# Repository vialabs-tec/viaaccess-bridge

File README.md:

# ViaAccess Bridge

Sidecar que conecta **Frigate** ao [ViaAccess](https://viaaccess.dev) via [VADP](https://viaaccess.dev/docs/detection-providers/vadp).

```
Câmeras → Frigate → MQTT → viaaccess-bridge → POST /api/v1/detections → ViaAccess
```

O bridge **não** faz reconhecimento facial nem cadastro de usuários. Ele traduz eventos de zona do Frigate em detecções de passagem (`passage_detected`) para auditoria no ViaAccess.

## Instalação

Pacote pronto com Frigate + MQTT + bridge: **[install/frigate/](install/frigate/README.md)**.

Leitor de QR na catraca + QR dinâmico Identity (Phase 1b): appliance
**[install/qr-reader-firmware/](install/qr-reader-firmware/README.md)** (ESP32-S3, ESP-IDF).
Contrato HTTP na porta 3710 e endpoints `/api/bridge/*` do Identity.

O agent Go em [install/qr-reader-agent/](install/qr-reader-agent/README.md) (Raspberry Pi)
é **legado**: código permanece no repo, CI desligado, sem novas instalações nem OTA de frota.

| | ESP32-S3 (suportado) |
|---|---|
| Leitor de QR | UART TTL 9600 (ex. EP8280L) ou `POST /scan` |
| Rede na primeira vez | SoftAP `viaaccess-setup` → `/wifi` |
| Mapa de GPIO | relé 10, porta 11, REX 12, LED 4/5/6 |
| Relógio | SNTP; DS3231 opcional para hora confiável sem rede |
| Contingência offline | Implementada (inclui `after_hours`) |
| OTA de frota | App image via comando `UPDATE` (`BRIDGE_OTA_*`) |

Provisionamento: cole a URL de claim (`clm_…`) do admin do Identity em
`http://viaaccess.local:3710/setup`.

Imagem Docker:

```text
ghcr.io/vialabs-tec/viaaccess-bridge:latest
```

```bash
cd install/frigate
cp .env.example .env   # API key + mapping
docker compose pull
docker compose up -d
```

Crie o tenant, o ponto de acesso (slug) e a API key no painel ViaAccess antes de subir o compose. Documentação completa: [viaaccess.dev/docs](https://viaaccess.dev/docs).

## Variáveis

| Variável | Descrição |
|----------|-----------|
| `VIAACCESS_API_URL` | URL da API ViaAccess |
| `VIAACCESS_API_KEY` | API key do tenant (`vac_…`) |
| `FRIGATE_MQTT_URL` | Broker MQTT (no compose: `mqtt://mqtt:1883`) |
| `FRIGATE_BASE_URL` | API HTTP do Frigate (snapshots) |
| `FRIGATE_ACCESS_POINT_MAP` | JSON: câmera + zona → slug do access point |
| `presenceSessionGapSeconds` | (por mapping) debounce de movimento contínuo no interior — ver README |
| `OUTBOX_PATH` | Fila de retry quando a API está offline |
| `BRIDGE_STATUS_PATH` | Arquivo JSON de status (opcional) |

## Desenvolvimento

```bash
npm install
cp .env.example .env
npm run dev
npm test
```

Build local da imagem: `npm run docker:build`

## Licença

Software proprietário © Via Labs. Uso sujeito aos termos do serviço ViaAccess.

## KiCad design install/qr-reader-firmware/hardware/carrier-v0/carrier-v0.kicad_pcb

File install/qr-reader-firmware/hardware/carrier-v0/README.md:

# Carrier v0 — KiCad project

Pilot interconnect PCB for the ESP32-S3 QR Reader appliance. Replaces Dupont
spaghetti: field screw terminals + module headers + 5 V star.

Spec: [`docs/carrier-v0.md`](../../docs/carrier-v0.md)

**Enclosure:** keep LOCK / DOOR / REX / READER screw terminals **inside** the
case. Field cables enter through **PG cable glands**; strain-relieve the jacket
(gland + cable tie) before the block. See *Case cable entry and strain relief*
in the spec — do not put live screw terminals on the outside of the case.
Mechanical project: [`../case-v0/`](../case-v0/) (FreeCAD workflow + OpenSCAD
skeleton).

| File | Role |
|---|---|
| `carrier-v0.kicad_pro` | KiCad 8+ project |
| `carrier-v0.kicad_pcb` | Board (footprints, routed nets, GND pour on `B.Cu`) |
| `carrier-v0.kicad_sch` | Net / connector index (minimal graphics) |
| `gen_pcb.py` | Regenerates the PCB (pad-accurate Manhattan routes) |
| `fab/` | JLCPCB Gerber/BOM/CPL notes |

Board size: **90 × 60 mm**, 2-layer, 1.6 mm.

Regenerate after layout edits in the script:

```bash
python3 gen_pcb.py
```

**Quit KiCad fully** (not only the PCB editor), then reopen `carrier-v0.kicad_pro`.
**Fill all zones**, then **DRC**.

### Routing status (v0)

Autorouted (corridor A\* on F/B + vias) with `B.Cu` GND pour. After regenerate:
quit KiCad fully → reopen → **Fill all zones** → **DRC**.
Pads-only fallback: `UNROUTED = True` in `gen_pcb.py`.

## Design choices

- **J1 DCIN** is a **XH 2P wafer** (pitch 2.5 mm, market “XH2.54”) for the
  female XH housing on the pigtail of a **panel-mount 5.5×2.1 mm** DC jack (P4).
  Pin 1 = `+5V`, pin 2 = `GND`. No field screw terminal for power.
- **J8A / J8B** are two **1×22** female headers (2.54 mm pitch) whose centers are
  **22.86 mm (0.9″)** apart — JLCPCB has no single dual-row 0.9″ part. Plug the
  DevKit **component-side up, USB to the left** (silk tick on J8A). Factory
  GPIOs/power on J8A (DevKit J1); J8B (DevKit J3) pads are NC keepouts.
  Pinout matches Espressif DevKitC-1 v1.1.
- **No BSS138 module.** Relay and buzzer use discrete **2N2222** open-collector
  drivers on the carrier (`Q2`/`R2`/`R3` and `Q1`/`R1`).
- **Relay (`J9`):** `IN` is pulled up to 5 V by `R3` (10k) and sunk by `Q2`
  when GPIO10 is high. In `/setup`, leave **relay active-high unchecked**
  (idle = GPIO high holds `IN` low / relay off; pulse drives GPIO low → `IN` high).
- **Buzzer (`J12`):** 2-wire active / SFM-20B. `+` → 5 V, `−` → `Q1` collector.
  In `/setup`, **buzzer active-high checked**.

### J8A / J8B DevKitC-1 nets (carrier)

USB end → far end. **J8A** = DevKit **J1**, **J8B** = DevKit **J3**.

| Socket | DevKit header | Pins netted on carrier |
|---|---|---|
| J8A | J1 | 3V3 (pin 1), GPIO 4–7, 17, 18, 8–12, 5V, GND |
| J8B | J3 | all NC on carrier (mechanical only) |

Reader UART on the carrier: GPIO17 = ESP RX, GPIO18 = ESP TX (factory map).

### NPN drivers (TO-92)

Pads left → right with flat face toward the silk “CBE” mark: **C – B – E**.

| Ref | C | B | E | Base resistor |
|---|---|---|---|---|
| Q2 (relay) | `RELAY_IN` | `Q2_BASE` | `GND` | R2 1k ← GPIO10 |
| Q1 (buzzer) | `BUZZ_SW` | `Q1_BASE` | `GND` | R1 1k ← GPIO7 |

Confirm against your transistor datasheet (2N2222 vs BC547 pinouts differ).

## Open in KiCad

1. Install [KiCad 8+](https://www.kicad.org/).
2. Open `carrier-v0.kicad_pro`.
3. Open the PCB: **Board Editor**.
4. Run **Fill all zones** (B.Cu GND pour) and **DRC**.
5. Tweak track positions if your module body keepouts need space.

The PCB was generated by script so expect to nudge silkscreen and re-pour GND
once before fab.

## Export Gerbers for JLCPCB

1. PCB Editor → **File → Fabrication Outputs → Gerbers** (`gerbers/`).
2. Enable layers: `F.Cu`, `B.Cu`, `F.SilkS`, `B.SilkS`, `F.Mask`, `B.Mask`, `Edge.Cuts`.
3. **Generate drill files** (Excellon).
4. Zip the `gerbers/` folder → upload to JLCPCB.
5. Options that usually work: 2 layers, 1.6 mm, HASL, 1 oz copper.

Suggested first order: **5 pcs**.

### PCBA (passives + sockets + connectors + NPNs)

BOM + centroid: [`fab/`](fab/) (`bom-jlcpcb.csv`, `cpl-jlcpcb.csv`, steps in `fab/README.md`).

- Enable **Standard** PCB Assembly (THT + SMT), top side.
- Assemble C1/C2, headers, screw terminals, DevKit socket, Q1/Q2, R1/R2/R3.
- **Do not** assemble DevKit / relay module / buzzer / LED / RTC — those plug in.

## Assembly notes

1. If bare PCB: solder SMDs (C2, R3), then THT (C1, transistors, headers, terminals).
   If PCBA, skip to continuity / module plug-in.
2. Continuity: `P5V` not shorted to `GND`.
3. Power via panel DC jack → J1 DCIN only: ~5 V on star, ~3.3 V on J8A pin 1.
4. `/setup`: relay **active-high off**; buzzer **active-high on**.
5. See checklist in `docs/carrier-v0.md`.

## BOM (carrier PCB)

| Ref | Part | Notes |
|---|---|---|
| J1 | XH 2P wafer (2.5 mm) | DCIN — mates jack pigtail XH female |
| J2 | Screw terminal 3P 5.08 | LOCK |
| J3, J4 | Screw terminal 2P 5.08 | DOOR, REX |
| J5 | Screw terminal 4P 5.08 | READER |
| J8A, J8B | Female header 1×22 ×2 | ESP32-S3-DevKitC-1 socket (0.9″ spacing) |
| J9, J10 | Pin header 1×3 | Relay control + dry |
| J12 | Pin header 1×2 | Buzzer (+ / switched −) |
| J13–J14 | Pin header 1×4 | LED, RTC |
| C1 | 1000 µF / ≥16 V radial | Star |
| C2 | 100 nF 0805 | Decouple |
| Q1, Q2 | 2N2222 TO-92 | Buzzer / relay drivers |
| R1, R2 | 1 kΩ axial | Base resistors |
| R3 | 10 kΩ 0805 | `RELAY_IN` pull-up to 5 V |
| — | Relay + modules | Plug into headers |

## Out of scope

On-board ESP32-S3 RF, PoE. Enclosure lives in [`../case-v0/`](../case-v0/), not
on this PCB. AliExpress “DevKitC” clones with a different pin order are **not**
supported on this socket — use Espressif DevKitC-1 (or a verified pin-compatible
board).

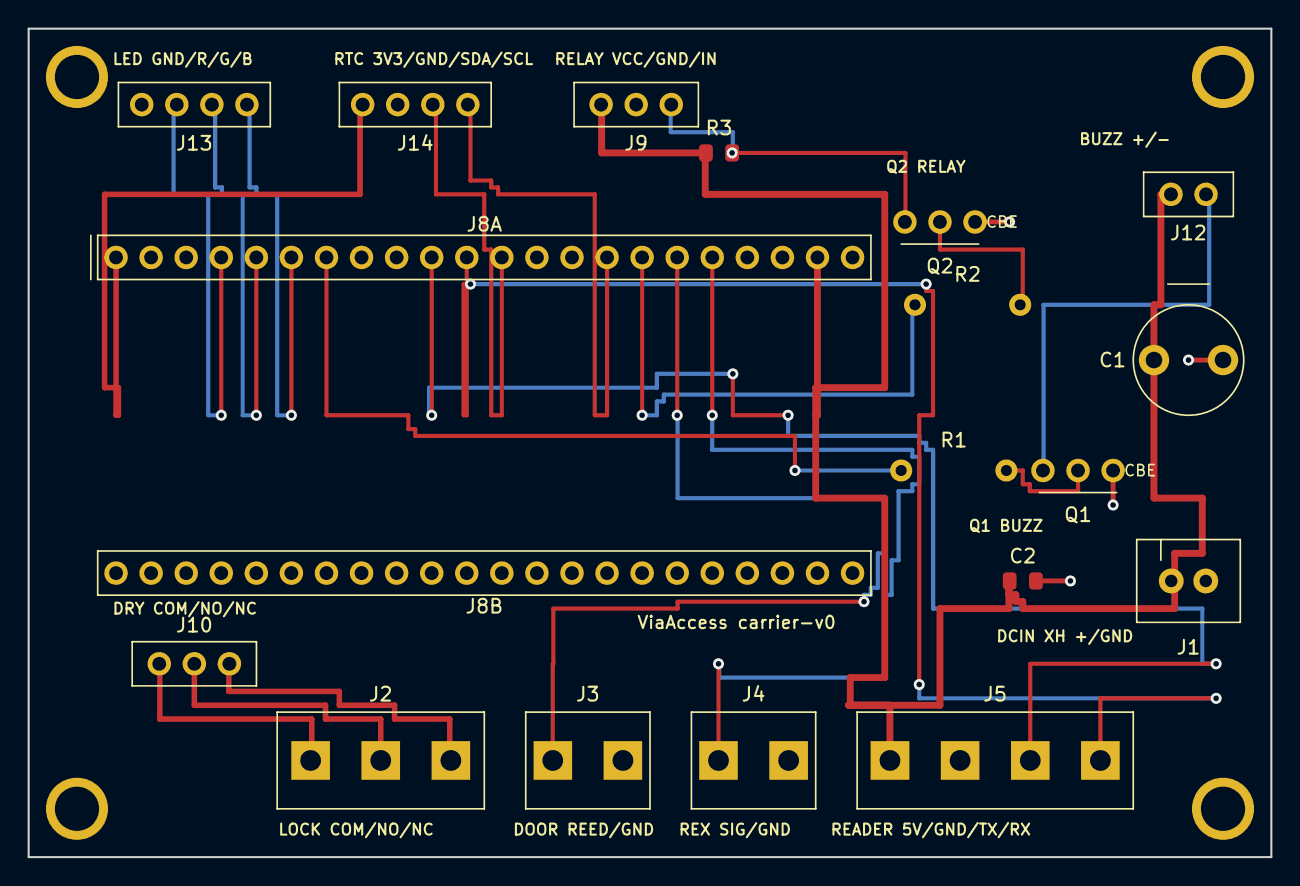
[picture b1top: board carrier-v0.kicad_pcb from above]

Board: 2 copper layers, 90.0 x 60.0 mm, 19 parts (0 on the bottom side), 21 nets.

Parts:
C1: 1000uF/16V; C_Radial
C2: 100n; C_0805
J1: DCIN; XH_1x02
J2: LOCK; Terminal_3P
J3: DOOR; Terminal_2P
J4: REX; Terminal_2P
J5: READER; Terminal_4P
J8A: DevKit-J1; PinSocket_1x22
J8B: DevKit-J3; PinSocket_1x22
J9: RELAY; PinHeader_1x03
J10: RELAY_DRY; PinHeader_1x03
J12: BUZZ; PinHeader_1x02
J13: LED; PinHeader_1x04
J14: RTC; PinHeader_1x04
Q1, Q2: 2N2222; TO92
R1, R2: 1k; R_Axial
R3: 10k; R_0805

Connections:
BUZZ_SW: J12.2, Q1.1
GND: C1.2, C2.2, J1.2, J3.2, J4.2, J5.2, J8A.22, J9.2, J13.1, J14.2, Q1.3, Q2.3
GPIO4: J8A.4, J13.2
GPIO5: J8A.5, J13.3
GPIO6: J8A.6, J13.4
GPIO7: J8A.7, R1.1
GPIO8: J8A.12, J14.3
GPIO9: J8A.15, J14.4
GPIO10: J8A.16, R2.1
GPIO11: J3.1, J8A.17
GPIO12: J4.1, J8A.18
GPIO17: J5.3, J8A.10
GPIO18: J5.4, J8A.11
LOCK_COM: J2.1, J10.1
LOCK_NC: J2.3, J10.3
LOCK_NO: J2.2, J10.2
P3V3: J8A.1, J14.1
P5V: C1.1, C2.1, J1.1, J5.1, J8A.21, J9.1, J12.1, R3.1
Q1_BASE: Q1.2, R1.2
Q2_BASE: Q2.2, R2.2
RELAY_IN: J9.3, Q2.1, R3.2

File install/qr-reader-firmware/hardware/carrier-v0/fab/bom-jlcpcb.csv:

Comment,Designator,Footprint,LCSC Part #
"100nF 50V X7R 0805 (decouple)",C2,C_0805,C49678
"10k 0805 1% (RELAY_IN pull-up)",R3,R_0805,C17414
"1000uF 16V electrolytic radial pitch 5mm (+ = pad1 left)",C1,C_Radial_P5,C439782
"XH 2P wafer pitch 2.5mm DCIN",J1,Connector_XH_2.50mm_1x02,C7429632
"Screw terminal 3P pitch 5.08mm (LOCK)",J2,TerminalBlock_3P_P5.08,C474953
"Screw terminal 2P pitch 5.08mm (DOOR)",J3,TerminalBlock_2P_P5.08,C8465
"Screw terminal 2P pitch 5.08mm (REX)",J4,TerminalBlock_2P_P5.08,C8465
"Screw terminal 4P pitch 5.08mm (READER)",J5,TerminalBlock_4P_P5.08,C53447001
"Female header 1x22 2.54mm TH (DevKit J1 row; pair with J8B at 22.86mm)",J8A,PinSocket_1x22_P2.54,C7499337
"Female header 1x22 2.54mm TH (DevKit J3 row; pair with J8A at 22.86mm)",J8B,PinSocket_1x22_P2.54,C7499337
"Pin header male 1x3 2.54mm (RELAY)",J9,PinHeader_1x03_P2.54,C2937625
"Pin header male 1x3 2.54mm (RELAY_DRY)",J10,PinHeader_1x03_P2.54,C2937625
"Pin header male 1x2 2.54mm (BUZZ)",J12,PinHeader_1x02_P2.54,C492401
"Pin header male 1x4 2.54mm (LED)",J13,PinHeader_1x04_P2.54,C2691448
"Pin header male 1x4 2.54mm (RTC)",J14,PinHeader_1x04_P2.54,C2691448
"2N2222A TO-92 NPN (buzzer) — confirm CBE pinout vs silk",Q1,TO92,C5330385
"2N2222A TO-92 NPN (relay) — confirm CBE pinout vs silk",Q2,TO92,C5330385
"1k axial carbon film D2.3xL6.5mm (Q1 base)",R1,R_Axial_P7.62,C120055
"1k axial carbon film D2.3xL6.5mm (Q2 base)",R2,R_Axial_P7.62,C120055
